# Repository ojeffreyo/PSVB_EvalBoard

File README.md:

# PSVB_EvalBoard
Hardware for SoC test designed by myself.

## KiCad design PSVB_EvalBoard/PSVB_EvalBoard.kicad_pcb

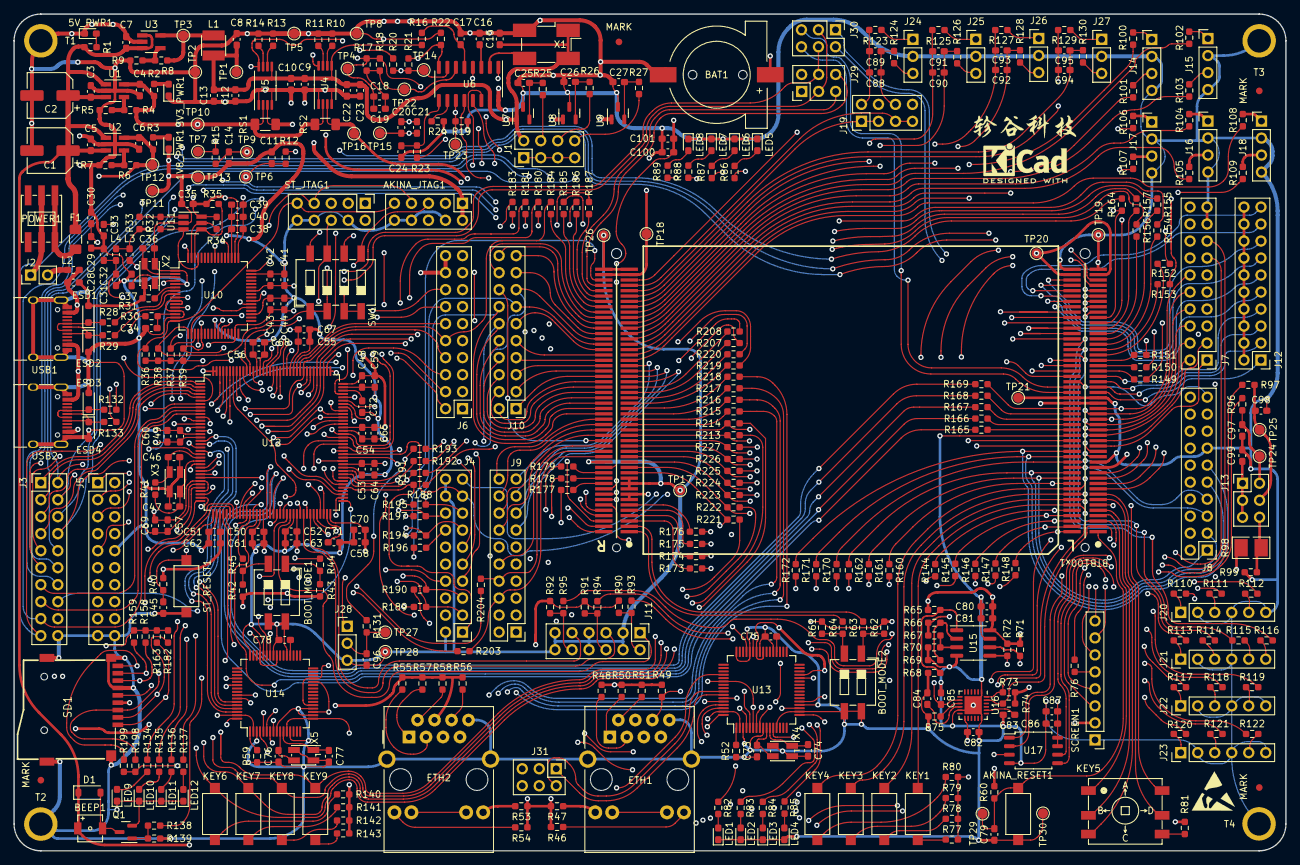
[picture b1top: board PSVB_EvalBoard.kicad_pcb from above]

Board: 4 copper layers, 190.0 x 125.0 mm, 463 parts (0 on the bottom side), 461 nets.

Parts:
1V8_PWR1: 0603 1V8_PWR; LED_0603_1608Metric_Pad1.05x0.95mm_HandSolder
3V3_PWR1: 0603 3V3_LED; LED_0603_1608Metric_Pad1.05x0.95mm_HandSolder
5V_PWR1: 0603 5V_LED; LED_0603_1608Metric_Pad1.05x0.95mm_HandSolder
AKINA_JTAG1: PinHeader_2x05_P2.54mm_Vertical
AKINA_RESET1: KEY; SW_SPST_CK_RS282G05A3
BAT1: CR1220-2; CR1220_Holder
BEEP1: BUZZER; BEEP_4317
BOOT_MODE1, BOOT_MODE2: SW_SMD_2P-2.54mm; SW_DIP_SPSTx02_Slide_6.7x6.64mm_W8.61mm_P2.54mm_LowProfile
BTB100x1: BTB100PINx2_IC_Adapter; BTB100PINx2_FemaleConnector
C1: 47uF; CP_Elec_6.3x7.7
C2: 22uF; CP_Elec_6.3x7.7
C3, C4, C5, C6, C7, C8: 0603 1uF/16V; C_0603_1608Metric_Pad1.08x0.95mm_HandSolder
C9: 0603 0.1uF/1%; C_0603_1608Metric_Pad1.08x0.95mm_HandSolder
C10, C17: 0603 4.7uF/1%; C_0603_1608Metric_Pad1.08x0.95mm_HandSolder
C11, C12, C14, C18, C19, C20, C21, C23, C29, C31, C34, C35, C45, C48, C71, C72, C75, C78, C79: 0603 0.1uF/16V; C_0603_1608Metric_Pad1.08x0.95mm_HandSolder
C13, C22, C24, C30, C32, C59: 0603 4.7uF/16V; C_0603_1608Metric_Pad1.08x0.95mm_HandSolder
C15: 0603 0.01uF/16V; C_0603_1608Metric_Pad1.08x0.95mm_HandSolder
C16: 0603 30P/16V; C_0603_1608Metric_Pad1.08x0.95mm_HandSolder
C25, C26, C27, C28: 0603 10uF/16V; C_0603_1608Metric_Pad1.08x0.95mm_HandSolder
C33: 0603 3.3uF/16V; C_0603_1608Metric_Pad1.08x0.95mm_HandSolder
C36, C37: 0603 27pF/16V; C_0603_1608Metric_Pad1.08x0.95mm_HandSolder
C38, C39, C40, C41, C42, C43, C44, C49, C50, C51, C52, C53, C54, C55, C56, C57, C58, C80, C81, C84, C85, C86, C87, C88, C89, C90, C91, C92, C93, C94, C95, C96, C97, C98, C99, C100: 0.1uF; C_0603_1608Metric_Pad1.08x0.95mm_HandSolder
C46, C47: 0603 10pF/16V; C_0603_1608Metric_Pad1.08x0.95mm_HandSolder
C60, C61, C62, C63, C64, C65, C67, C68, C69, C70: 4.7uF; C_0603_1608Metric_Pad1.08x0.95mm_HandSolder
C73, C74, C76, C77: 0603 20PF/16V; C_0603_1608Metric_Pad1.08x0.95mm_HandSolder
C82: 0.01uF; C_0603_1608Metric_Pad1.08x0.95mm_HandSolder
C83: 2.2nF; C_0603_1608Metric_Pad1.08x0.95mm_HandSolder
C101: 10uF; C_0603_1608Metric_Pad1.08x0.95mm_HandSolder
D1: 1N4148; D_SOD-123
ESD1, ESD2, ESD3, ESD4: SD24C-TP; D_SOD-323_HandSoldering
ETH1, ETH2: HR911105A; RJ45_HanRun_HR911105A
F1: 1206 10V/2A; Fuse_1206_3216Metric_Pad1.42x1.75mm_HandSolder
J1, J19: PinHeader_2x04_P2.54mm_Vertical
J2: PIN2; PinHeader_1x02_P2.54mm_Vertical
J3, J4, J5, J6, J7, J8, J9, J10, J12: PIN20; PinHeader_2x10_P2.54mm_Vertical
J11: PIN12_2x6; PinHeader_2x06_P2.54mm_Vertical
J13, J29, J30, J31: PIN6_2x3; PinHeader_2x03_P2.54mm_Vertical
J14, J15, J16, J17, J18: PinHeader_1x04_P2.54mm_Vertical
J20, J21, J22, J23: PinHeader_1x06_P2.54mm_Vertical
J24, J25, J26, J27, J28: PinHeader_1x03_P2.54mm_Vertical
KEY1, KEY2, KEY3, KEY4, KEY6, KEY7, KEY8, KEY9: SW_Push; SW_SPST_CK_RS282G05A3
KEY5: 5Axises_KEY; 5Axises_Key
L1: 2.2uH/1A; SWPA3010
L2, L3, L4: 6.8nH/500mA; L_0603_1608Metric_Pad1.05x0.95mm_HandSolder
LED1, LED2: YELLOW; LED_0603_1608Metric_Pad1.05x0.95mm_HandSolder
LED3, LED4, LED5, LED6, LED7, LED8, LED9, LED10, LED11, LED12: LD271; LED_0603_1608Metric_Pad1.05x0.95mm_HandSolder
MARK: Fiducial_1mm_Mask2mm
MARK#2, MARK#3, MARK#4: Fiducial_1mm_Mask2mm
POWER1: SW_SELF_LOCK_5.8mm-5.8mm-10mm; SelfLock_Switch
Q1: S9013; SOT-23
R1: 0603 5K/1%; R_0603_1608Metric_Pad0.98x0.95mm_HandSolder
R2, R3, R134, R135, R136, R137, R138: 0603 1K/1%; R_0603_1608Metric_Pad0.98x0.95mm_HandSolder
R4, R8: 0603 500K/1%; R_0603_1608Metric_Pad0.98x0.95mm_HandSolder
R5, R7: 0603 160K/1%; R_0603_1608Metric_Pad0.98x0.95mm_HandSolder
R6: 0603 200K/1%; R_0603_1608Metric_Pad0.98x0.95mm_HandSolder
R9: 0603 160K/16V; R_0603_1608Metric_Pad0.98x0.95mm_HandSolder
R10, R11, R12, R13, R14, R15, R17, R18, R19, R20, R21, R22, R23, R24, R25, R26, R27, R28, R29: 0603 0R/1%; R_0603_1608Metric_Pad0.98x0.95mm_HandSolder
R16, R30, R33, R34, R35, R36, R37, R38, R39, R40, R42, R43, R44, R45, R60, R61, R62, R63, R64, R76, R139, R140, R141, R142, R143, R144, R145, R146, R147, R148, R149, R150, R151, R152, R153, R154, R155, R156, R157, R160, R161, R162, R164, R165, R166, R167, R168, R169, R170, R171, R172, R173, R174, R175, R176, R177, R178, R179, R180, R181, R183, R184, R185, R186, R187, R188, R189, R190, R191, R192, R193, R194, R195, R196, R197, R203, R204, R207, R208, R213, R214, R215, R216, R217, R218, R219, R220, R221, R222, R223, R224, R225, R226, R227: 0603 10K/1%; R_0603_1608Metric_Pad0.98x0.95mm_HandSolder
R31: 0603 12K/1%; R_0603_1608Metric_Pad0.98x0.95mm_HandSolder
R32: 0603 2K/1%; R_0603_1608Metric_Pad0.98x0.95mm_HandSolder
R41: 0603 1M/1%; R_0603_1608Metric_Pad0.98x0.95mm_HandSolder
R46, R47, R53, R54: 510R/1%; R_0603_1608Metric_Pad0.98x0.95mm_HandSolder
R48, R49, R50, R51, R55, R56, R57, R58: 49R9/1%; R_0603_1608Metric_Pad0.98x0.95mm_HandSolder
R52, R59: 18K/1%; R_0603_1608Metric_Pad0.98x0.95mm_HandSolder
R65, R66, R67, R68, R69, R70, R71, R72, R73, R74, R77, R78, R79, R80, R81, R90, R91, R92, R96, R97, R99, R123, R124, R125, R126, R127, R128, R129, R130: 10K/1%; R_0603_1608Metric_Pad0.98x0.95mm_HandSolder
R75: 4.7K/1%; R_0603_1608Metric_Pad0.98x0.95mm_HandSolder
R82, R83, R84, R85, R86, R87, R88, R89: 1K/1%; R_0603_1608Metric_Pad0.98x0.95mm_HandSolder
R93, R94, R95, R100, R101, R102, R103, R104, R105, R106, R107, R108, R109, R110, R111, R112, R113, R114, R115, R116, R117, R118, R119, R120, R121, R122, R132, R133: 0R/1%; R_0603_1608Metric_Pad0.98x0.95mm_HandSolder
R98: A1050; GT36516
R131: 0603 100R/1%; R_0603_1608Metric_Pad0.98x0.95mm_HandSolder
R158, R159, R163, R182, R198, R199: 0603 47K/1%; R_0603_1608Metric_Pad0.98x0.95mm_HandSolder
RS1, RS2: 0603 10mR/1%; R_1206_3216Metric_Pad1.30x1.75mm_HandSolder
SCREEN1: 2.4In_TFT_Screen; PinHeader_1x08_P2.54mm_Vertical
SD1: TF-SMD_TF-02
ST_JTAG1: PinHeader_2x05_P2.54mm_Vertical
ST_RESET1: KEY; SW_SPST_CK_RS282G05A3
SW1: SW_DIP_SPSTx04_Slide_6.7x11.72mm_W8.61mm_P2.54mm_LowProfile
T1, T2, T3, T4: M3_Whole
TP1, TP2, TP3, TP4, TP5, TP6, TP7, TP8, TP9, TP10, TP11, TP12, TP13, TP14, TP15, TP16, TP17, TP18, TP19, TP20, TP21, TP22, TP23, TP24, TP25, TP26, TP27, TP28, TP29, TP30: TestPoint_1.5mm; TestPoint_Pad_D1.5mm
U1, U2, U3: SGM2036-ADJ; SOT-23-5_HandSoldering
U4, U5: INA240A1PWR; TSSOP-8_4.4x3mm_P0.65mm
U6: TM7707; SOIC-16_3.9x9.9mm_P1.27mm
U7: REF3030; SOT-23
U8: REF3025; SOT-23
U9: REF3012; SOT-23
U10: LQFP-64_10x10mm_P0.5mm
U11: 93LC56BT-IOT; SOT-23-6_Handsoldering
U12: STM32F429ZETx; LQFP-144_20x20mm_P0.5mm
U13, U14: CH395Q; LQFP-64_10x10mm_P0.5mm
U15: 24LC64ISN; SOIC-8_3.9x4.9mm_P1.27mm
U16: MPU6050; QFN-24-1EP_4x4mm_P0.5mm_EP2.7x2.6mm
U17: W25Q128JVSIQ; SOIC-8_5.275x5.275mm_P1.27mm
USB1, USB2: USB_C_16PIN-Connector; USB_C_PIN16
X1: 2.4576Mhz; Oscillator_SMD_EuroQuartz_XO91-4Pin_7.0x5.0mm_HandSoldering
X2: 12Mhz_Passive_3225; Oscillator_SMD_EuroQuartz_XO32-4Pin_3.2x2.5mm_HandSoldering
X3: 16Mhz_Passive_3225; Oscillator_SMD_EuroQuartz_XO32-4Pin_3.2x2.5mm_HandSoldering
X4, X5: 30Mhz_3225; Oscillator_SMD_EuroQuartz_XO32-4Pin_3.2x2.5mm_HandSoldering

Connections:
+1V8: C6.1, R3.2, R6.2, R46.2, R47.2, R53.2, R54.2, TP12.1, U2.5 (VOUT), U13.6 (VCC18), U13.19 (VCC18), U13.28 (VCC18), U13.43 (VCC18), U13.54 (VCC18), U13.64 (VCC18), U14.6 (VCC18), U14.19 (VCC18), U14.28 (VCC18), U14.43 (VCC18), U14.54 (VCC18), U14.64 (VCC18)
+3.3VA: C8.1, C9.2, C10.2, C12.2, C13.2, C15.1, C22.1, C23.1, J1.2, L1.2, R16.2, TP1.1, U4.5 (VCC), U5.5 (VCC), U6.15 (VDD), U7.1 (IN), U8.1 (IN), U9.1 (IN), X1.1 (OE), X1.4 (VDD)
+3V3: AKINA_JTAG1.1, AKINA_JTAG1.2, C4.1, C35.1, C41.2, C42.2, C43.2, C44.2, C48.1, C49.1, C50.1, C51.1, C52.1, C53.1, C54.1, C55.1, C56.1, C57.1, C58.1, C59.1, C60.1, C61.1, C62.1, C63.1, C64.1, C65.1, C67.1, C68.1, C69.1, C70.1, C80.1, C81.1, C82.1, C85.1, C86.1, C87.1, ETH1.4 (P4/CT), ETH1.5 (P5/CT), ETH2.4 (P4/CT), ETH2.5 (P5/CT), J5.2, J5.4, J6.18, J6.20, L3.2, L4.2, R2.2, R4.2, R30.1, R33.1, R34.2, R35.2, R36.1, R37.1, R38.1, R39.1, R40.1, R42.2, R43.2, R48.1, R49.1, R50.1, R51.1, R55.1, R56.1, R57.1, R58.1, R61.2, R62.2, R65.1, R66.1, R67.1, R71.1, R72.1, R73.1, R74.1, R77.2, R78.2, R79.2, R80.2, R81.2, R90.2, R91.2, R92.2, R98.1, R140.2, R141.2, R142.2, R143.2, R158.2, R159.2, R163.2, R182.2, R198.2, R199.2, RS1.1, RS2.1, SCREEN1.2 (VCC), SD1.4 (VDD), ST_JTAG1.1, ST_JTAG1.2, TP10.1, U1.5 (VOUT), U4.2 (IN+), U5.2 (IN+), U10.20 (VCCIO), U10.31 (VCCIO), U10.42 (VCCIO), U10.50 (VREGIN), U10.56 (VCCIO), U11.6 (VCC), U12.17 (VDD), U12.30 (VDD), U12.33 (VDDA), U12.39 (VDD), U12.52 (VDD), U12.62 (VDD), U12.72 (VDD), U12.84 (VDD), U12.95 (VDD), U12.108 (VDD), U12.121 (VDD), U12.131 (VDD), U12.143 (PDR_ON), U12.144 (VDD), U13.2 (VCC33), U13.12 (VCC33), U13.17 (VCC33), U13.21 (VCC33), U13.29 (VCC33), U13.40 (VCC33), U13.42 (VCC33), U13.45 (VCC33), U13.63 (VCC33), U14.2 (VCC33), U14.12 (VCC33), U14.17 (VCC33), U14.21 (VCC33), U14.29 (VCC33), U14.40 (VCC33), U14.42 (VCC33), U14.45 (VCC33), U14.63 (VCC33), U15.8 (VCC), U16.8 (VLOGIC), U16.13 (VDD), U17.3 (~WP(IO2)), U17.7 (~HOLD/RESET(IO3)), U17.8 (VCC)
+5V: BEEP1.1 (+), BTB100x1.107, BTB100x1.108, C1.1, C2.1, C3.1, C5.1, C7.1, D1.1 (K), F1.1, R1.1, U1.1 (VIN), U1.3 (EN), U2.1 (VIN), U2.3 (EN), U3.1 (VIN), U3.3 (EN)
/AD0: AKINA_JTAG1.9, BTB100x1.154, R36.2, ST_JTAG1.9, U10.16 (ADBUS0), U12.109 (PA14)
/AD1: AKINA_JTAG1.5, BTB100x1.152, R38.2, SW1.1, SW1.2, SW1.5, U10.17 (ADBUS1)
/AD2: SW1.3, SW1.4, U10.18 (ADBUS2)
/AD3: AKINA_JTAG1.7, BTB100x1.153, R37.2, ST_JTAG1.7, U10.19 (ADBUS3), U12.105 (PA13)
/AD4: AKINA_JTAG1.3, BTB100x1.155, R39.2, ST_JTAG1.3, U10.21 (ADBUS4), U12.134 (PB4)
/ADC12_IN14: C14.1, R15.2, TP9.1, U12.44 (PC4)
/ADC12_IN15: C11.2, R12.2, TP6.1, U12.45 (PC5)
/ADC123_IN13: J28.1, U12.29 (PC3)
/AIN1+: C20.1, C21.1, R20.2, R21.2, TP14.1, U6.7 (AIN1(+))
/AIN1-: C20.2, C21.2, R21.1, R22.2, TP15.1, U6.8 (AIN1(-))
/AIN2+: C18.1, C19.1, R17.2, R18.2, TP22.1, U6.6 (AIN2(+))
/AIN2-: C18.2, C19.2, R12.1, R17.1, R18.1, R19.2, TP4.1, TP23.1, U4.8 (OUT), U6.11 (AIN2(-))
/AKINA_ADC_IN4: BTB100x1.27, J12.1
/AKINA_ADC_IN5: BTB100x1.28, J12.3
/AKINA_ADC_IN6: BTB100x1.29, J12.5
/AKINA_ADC_IN7: BTB100x1.30, J12.7
/AKINA_ADC_IN8: BTB100x1.93, J12.9
/AKINA_ADC_IN9: BTB100x1.94, J12.11
/AKINA_ADC_IN10: BTB100x1.97, J12.13
/AKINA_ADC_IN11: BTB100x1.98, J12.15
/AKINA_ADC_IN12: BTB100x1.96, J12.17
/AKINA_ADC_IN13: BTB100x1.95, J12.19
/AKINA_BLK: BTB100x1.21, J7.6, SCREEN1.8 (BLK)
/AKINA_BOOT0: BTB100x1.101, R64.2
/AKINA_BOOT1: BTB100x1.102, R63.2
/AKINA_CMP1_IN: BTB100x1.86, R116.1
/AKINA_CMP1_IP1: BTB100x1.80, R110.1
/AKINA_CMP1_IP2: BTB100x1.81, R111.1
/AKINA_CMP1_IP3: BTB100x1.82, R112.1
/AKINA_CMP1_IP4: BTB100x1.84, R114.1
/AKINA_CMP1_IP5: BTB100x1.85, R115.1
/AKINA_CMP1/2_REF: BTB100x1.83, R113.1
/AKINA_CMP2_IN: BTB100x1.92, R122.1
/AKINA_CMP2_IP1: BTB100x1.87, R117.1
/AKINA_CMP2_IP2: BTB100x1.88, R118.1
/AKINA_CMP2_IP3: BTB100x1.89, R119.1
/AKINA_CMP2_IP4: BTB100x1.90, R120.1
/AKINA_CMP2_IP5: BTB100x1.91, R121.1
/AKINA_D_C: BTB100x1.20, J7.4, SCREEN1.6 (D/C)
/AKINA_ETH_ELINK: ETH1.10, ETH1.11, U13.52 (ELINK#)
/AKINA_ETH_SCK: BTB100x1.170, J9.16, U13.60 (SCK)
/AKINA_ETH_SCS: BTB100x1.169, J9.14, U13.59 (SCS)
/AKINA_ETH_SDI: BTB100x1.171, J9.18, U13.61 (SDI)
/AKINA_ETH_SDO: BTB100x1.172, J9.20, U13.62 (SDO)
/AKINA_HALL_CH1: BTB100x1.46, R93.2
/AKINA_HALL_CH2: BTB100x1.47, R94.2
/AKINA_HALL_CH3: BTB100x1.48, R95.2
/AKINA_I2C1_SCL: BTB100x1.17, J7.1, R71.2, U15.6 (SCL)
/AKINA_I2C1_SDA: BTB100x1.18, J7.3, R72.2, U15.5 (SDA)
/AKINA_I2C2_SCL: BTB100x1.2, J7.13, R74.2, U16.23 (SCL)
/AKINA_I2C2_SDA: BTB100x1.3, J7.15, R73.2, U16.24 (SDA)
/AKINA_JTDO: AKINA_JTAG1.6, BTB100x1.151, SW1.6
/AKINA_KEY1: BTB100x1.56, J8.12, KEY1.1
/AKINA_KEY2: BTB100x1.57, J8.14, KEY2.1
/AKINA_KEY3: BTB100x1.58, J8.16, KEY3.1
/AKINA_KEY4: BTB100x1.59, J8.18, KEY4.1
/AKINA_KEY_A: BTB100x1.4, KEY5.1 (A)
/AKINA_KEY_B: BTB100x1.5, KEY5.2 (B)
/AKINA_KEY_C: BTB100x1.7, KEY5.3 (C)
/AKINA_KEY_CENTER: BTB100x1.6, KEY5.6 (CENTER)
/AKINA_KEY_D: BTB100x1.8, KEY5.5 (D)
/AKINA_LED0: BTB100x1.42, J7.14, R89.1
/AKINA_LED1: BTB100x1.43, J7.16, R88.1
/AKINA_LED2: BTB100x1.44, J7.18, R87.1
/AKINA_LED3: BTB100x1.45, J7.20, R86.1
/AKINA_LED4: BTB100x1.156, R85.1
/AKINA_LED5: BTB100x1.157, R84.1
/AKINA_LED6: BTB100x1.158, R83.1
/AKINA_LED7: BTB100x1.159, R82.1
/AKINA_OPAMP1_IN: C88.1, C89.1, J19.6, R124.1
/AKINA_OPAMP1_IP: C88.2, C89.2, J19.2, R123.1
/AKINA_OPAMP2_IN: BTB100x1.142, C90.1, C91.1, R126.1
/AKINA_OPAMP2_IP: BTB100x1.143, C90.2, C91.2, R125.1
/AKINA_OPAMP3_IN: BTB100x1.140, C92.1, C93.1, R128.1
/AKINA_OPAMP3_IP: BTB100x1.141, C92.2, C93.2, R127.1
/AKINA_OPAMP4_IN: BTB100x1.145, C94.1, C95.1, R130.1
/AKINA_OPAMP4_IP: BTB100x1.144, C94.2, C95.2, R129.1
/AKINA_OPA_OUT: BTB100x1.198, R131.2
/AKINA_PA9: BTB100x1.147, J19.5, J19.7
/AKINA_PA10: BTB100x1.146, J19.1, J19.3
/AKINA_RESET: AKINA_RESET1.2, BTB100x1.1, C79.1, R60.1, TP29.1
/AKINA_SCREEN_RST: BTB100x1.19, J7.2, R76.2
/AKINA_SPI1_MISO: BTB100x1.10, J7.7, U17.2 (DO(IO1))
/AKINA_SPI1_MOSI: BTB100x1.11, J7.9, U17.5 (DI(IO0))
/AKINA_SPI1_NSS: BTB100x1.12, J7.11, U17.1 (~CS)
/AKINA_SPI1_SCK: BTB100x1.9, J7.5, U17.6 (CLK)
/AKINA_SPI2_MOSI: BTB100x1.23, J7.10, SCREEN1.4 (SDA)
/AKINA_SPI2_NSS: BTB100x1.24, J7.12, SCREEN1.7 (CS)
/AKINA_SPI2_SCK: BTB100x1.22, J7.8, SCREEN1.3 (SCL)
/AKINA_USART1_RX: BTB100x1.16, J29.2
/AKINA_USART1_TX: BTB100x1.15, J29.1
/AKINA_USART2_RX: BTB100x1.197, J29.6
/AKINA_USART2_TX: BTB100x1.196, J29.5
/AKINA_USART3_RX: BTB100x1.68, J30.2
/AKINA_USART3_TX: BTB100x1.67, J30.1
/AKINA_USART4_RX: BTB100x1.78, J30.6
/AKINA_USART4_TX: BTB100x1.77, J30.5
/BTB_PA0: BTB100x1.103, R173.1
/BTB_PA1: BTB100x1.104, R174.1
/BTB_PA2: BTB100x1.105, R175.1
/BTB_PA3: BTB100x1.106, R176.1
/BTB_PB0: BTB100x1.165, J9.6, R203.1
/BTB_PB1: BTB100x1.166, J9.8, R204.1
/BTB_PB2: BTB100x1.167, J9.10
/BTB_PB5: BTB100x1.128, R208.1
/BTB_PC0: BTB100x1.60, J8.20, R160.1
/BTB_PC1: BTB100x1.61, J8.1, R161.1
/BTB_PC2: BTB100x1.62, J8.3, R162.1
/BTB_PC6: BTB100x1.173, J10.14, R196.1
/BTB_PC7: BTB100x1.174, J10.12, R197.1
/BTB_PC13: BTB100x1.64, J8.7, R170.2
/BTB_PC14: BTB100x1.65, J8.9, R171.2
/BTB_PC15: BTB100x1.66, J8.11, R172.2
/BTB_PD0: BTB100x1.188, J10.17, R180.1
/BTB_PD1: BTB100x1.189, J10.19, R181.1
/BTB_PD3: BTB100x1.190, J10.20, R183.1
/BTB_PD4: BTB100x1.192, R184.1
/BTB_PD5: BTB100x1.193, R185.1
/BTB_PD6: BTB100x1.194, R186.1
/BTB_PD7: BTB100x1.195, R187.1
/BTB_PD8: BTB100x1.180, J10.1, R188.1
/BTB_PD9: BTB100x1.181, J10.3, R189.1
/BTB_PD10: BTB100x1.182, J10.5, R190.1
/BTB_PD11: BTB100x1.183, J10.7, R191.1
/BTB_PD12: BTB100x1.184, J10.9, R192.1
/BTB_PD13: BTB100x1.185, J10.11, R193.1
/BTB_PD14: BTB100x1.186, J10.13, R194.1
/BTB_PD15: BTB100x1.187, J10.15, R195.1
/BTB_PE0: BTB100x1.125, R219.1
/BTB_PE1: BTB100x1.126, R220.1
/BTB_PE2: BTB100x1.51, J8.2, R148.2
/BTB_PE3: BTB100x1.52, J8.4, R147.2
/BTB_PE4: BTB100x1.53, J8.6, R146.2
/BTB_PE5: BTB100x1.54, J8.8, R145.2
/BTB_PE6: BTB100x1.55, J8.10, R144.2
/BTB_PE7: BTB100x1.119, J9.9, R213.1
/BTB_PE8: BTB100x1.120, J9.11, R214.1
/BTB_PE10: BTB100x1.121, R215.1
/BTB_PE12: BTB100x1.122, R216.1
/BTB_PE14: BTB100x1.123, R217.1
/BTB_PE15: BTB100x1.124, R218.1
/BTB_PF0: BTB100x1.31, R149.2
/BTB_PF1: BTB100x1.32, R150.2
/BTB_PF2: BTB100x1.33, R151.2
/BTB_PF3: BTB100x1.34, R152.2
/BTB_PF4: BTB100x1.35, R153.2
/BTB_PF5: BTB100x1.36, R154.2
/BTB_PF6: BTB100x1.37, R155.2
/BTB_PF7: BTB100x1.38, R156.2
/BTB_PF8: BTB100x1.39, R157.2
/BTB_PF9: BTB100x1.40, J8.15
/BTB_PF10: BTB100x1.41, J8.17, R164.1
/BTB_PF11: BTB100x1.70, R165.1
/BTB_PF12: BTB100x1.71, R166.1
/BTB_PF13: BTB100x1.72, R167.1
/BTB_PF14: BTB100x1.73, R168.1
/BTB_PF15: BTB100x1.74, R169.1
/BTB_PG0: BTB100x1.112, J9.1, R221.1
/BTB_PG1: BTB100x1.113, J9.2, R222.1
/BTB_PG2: BTB100x1.114, J9.4, R223.1
/BTB_PG3: BTB100x1.115, J9.3, R224.1
/BTB_PG4: BTB100x1.116, J9.5, R225.1
/BTB_PG5: BTB100x1.117, J9.7, R226.1
/BTB_PG6: BTB100x1.118, J9.12, R227.1
/BTB_PG9: BTB100x1.160, R177.1
/BTB_PG10: BTB100x1.161, R178.1
/BTB_PG11: BTB100x1.162, R179.1
/BTB_PG15: BTB100x1.127, R207.1
/CMP1_IN: J21.5, R115.2
/CMP1_IP1: J20.1, R110.2
/CMP1_IP2: J20.3, R111.2
/CMP1_IP3: J20.5, R112.2
/CMP1_IP4: J21.1, R113.2
/CMP1_IP5: J21.3, R114.2
/CMP2_IN: J23.5, R122.2
/CMP2_IP1: J22.1, R117.2
/CMP2_IP2: J22.3, R118.2
/CMP2_IP3: J22.5, R119.2
/CMP2_IP4: J23.1, R120.2
/CMP2_IP5: J23.3, R121.2
/DUT_+3.3V_1: BTB100x1.25, BTB100x1.49, BTB100x1.75, BTB100x1.99, BTB100x1.149, BTB100x1.199, R60.2, RS1.2, TP18.1, TP20.1, U5.3 (IN-)
/DUT_VBAT: BAT1.1 (+), BTB100x1.163, C100.1, C101.1, U12.6 (VBAT)
/DUT_VDDA_3.3V_1: BTB100x1.13, RS2.2, TP16.1, U4.3 (IN-)
/ETH1_RXD: J31.2, U13.57 (RXD)
/ETH1_RXN: ETH1.6 (P6/RD-), R49.2, U13.5 (RXN)
/ETH1_RXP: ETH1.3 (P3/RD+), R48.2, U13.4 (RXP)
/ETH1_TXD: J31.1, U13.58 (TXD)
/ETH1_TXN: ETH1.2 (P2/TD-), R51.2, U13.8 (TXN)
/ETH1_TXP: ETH1.1 (P1/TD+), R50.2, U13.7 (TXP)
/ETH2_RXD: J31.6, U14.57 (RXD)
/ETH2_RXN: ETH2.6 (P6/RD-), R56.2, U14.5 (RXN)
/ETH2_RXP: ETH2.3 (P3/RD+), R55.2, U14.4 (RXP)
/ETH2_TXD: J31.5, U14.58 (TXD)
/ETH2_TXN: ETH2.2 (P2/TD-), R58.2, U14.8 (TXN)
/ETH2_TXP: ETH2.1 (P1/TD+), R57.2, U14.7 (TXP)
/EXP_PIN1: BTB100x1.63, J8.5
/EXP_PIN2: BTB100x1.79, J8.19
/EXP_PIN3: BTB100x1.129, J9.13
/EXP_PIN4: BTB100x1.130, J9.15
/EXP_PIN5: BTB100x1.131, J9.17
/EXP_PIN6: BTB100x1.132, J9.19
/EXP_PIN7: BTB100x1.168, J10.16
/EXP_PIN8: BTB100x1.175, J10.10
/EXP_PIN9: BTB100x1.176, J10.8
/EXP_PIN10: BTB100x1.177, J10.6
/EXP_PIN11: BTB100x1.178, J10.4
/EXP_PIN12: BTB100x1.179, J10.2
/EXP_PIN13: BTB100x1.191, J10.18
/FT_USART2_RX: J29.3, J30.3, U10.27 (BDBUS1)
/FT_USART2_TX: J29.4, J30.4, U10.26 (BDBUS0)
/FT_USART3_RX: U10.39 (CDBUS1), U12.69 (PB10)
/FT_USART3_TX: U10.38 (CDBUS0), U12.70 (PB11)
/FT_USART4_RX: J31.3, U10.52 (DDBUS1)
/FT_USART4_TX: J31.4, U10.48 (DDBUS0)
/INA240_Output1: R15.1, R20.1, TP7.1, U5.8 (OUT)
/MCPWM_CH1: BTB100x1.134, R100.1
/MCPWM_CH1N: BTB100x1.135, R101.1
/MCPWM_CH2: BTB100x1.139, R102.1
/MCPWM_CH2N: BTB100x1.138, R103.1
/MCPWM_CH3: BTB100x1.137, R104.1
/MCPWM_CH3N: BTB100x1.136, R105.1
/MCPWM_CH4: J19.4, R106.1
/MCPWM_CH4N: J19.8, R107.1
/MC_BKIN_0: BTB100x1.133, R108.1
/MC_BKIN_1: BTB100x1.148, R109.1
/OPAMP1_IN: J24.3, R124.2
/OPAMP1_IP: J24.1, R123.2
/OPAMP2_IN: J25.3, R126.2
/OPAMP2_IP: J25.1, R125.2
/OPAMP3_IN: J26.3, R128.2
/OPAMP3_IP: J26.1, R127.2
/OPAMP4_IN: J27.3, R130.2
/OPAMP4_IP: J27.1, R129.2
/PA0: J5.7, KEY6.1, R173.2, U12.34 (PA0)
/PA1: J5.9, KEY7.1, R174.2, U12.35 (PA1)
/PA2: J5.11, KEY8.1, R175.2, U12.36 (PA2)
/PA3: J5.13, KEY9.1, R176.2, U12.37 (PA3)
/PA6: J5.15, U12.42 (PA6)
/PA7: J5.17, U12.43 (PA7)
/PA8: J6.5, U12.100 (PA8)
/PA9: J6.7, U12.101 (PA9)
/PA10: J6.9, U12.102 (PA10)
/PA11: J6.11, U12.103 (PA11)
/PA12: J6.13, U12.104 (PA12)
/PB0: J5.6, R203.2, U12.46 (PB0)
/PB1: J5.8, R204.2, U12.47 (PB1)
/PB5: R208.2, U12.135 (PB5)
/PB6: R137.1, U12.136 (PB6)
/PB7: R136.1, U12.137 (PB7)
/PB8: R135.1, U12.139 (PB8)
/PB9: R134.1, U12.140 (PB9)
/PC0: J5.1, R160.2, U12.26 (PC0)
/PC1: J5.3, R161.2, U12.27 (PC1)
/PC2: J5.5, R162.2, U12.28 (PC2)
/PC6: J4.14, R196.2, U12.96 (PC6)
/PC7: J4.16, R197.2, U12.97 (PC7)
/PC8: J6.1, R158.1, SD1.7 (DAT0(D0)), U12.98 (PC8)
/PC9: J6.3, R159.1, SD1.8 (DAT1(RSV)), U12.99 (PC9)
/PC10: J6.15, R163.1, SD1.1 (DAT2(RSV)), U12.111 (PC10)
/PC11: J6.17, R182.1, SD1.2 (CDAT3/CS), U12.112 (PC11)
/PC12: J6.19, SD1.5 (CLK), U12.113 (PC12)
/PC13: J3.11, R170.1, U12.7 (PC13)
/PC14: J3.13, R171.1, U12.8 (PC14)
/PC15: J3.15, R172.1, U12.9 (PC15)
/PD0: J6.2, R180.2, U12.114 (PD0)
/PD1: J6.4, R181.2, U12.115 (PD1)
/PD2: J6.6, R198.1, SD1.3 (CMD), U12.116 (PD2)
/PD3: J6.8, R183.2, R199.1, SD1.9 (CD), U12.117 (PD3)
/PD4: J6.10, R184.2, U12.118 (PD4)
/PD5: J6.12, R185.2, U12.119 (PD5)
/PD6: J6.14, R186.2, U12.122 (PD6)
/PD7: J6.16, R187.2, U12.123 (PD7)
/PD8: J4.1, R188.2, U12.77 (PD8)
/PD9: J4.3, R189.2, U12.78 (PD9)
/PD10: J4.5, R190.2, U12.79 (PD10)
/PD11: J4.7, R191.2, U12.80 (PD11)
/PD12: J4.9, R192.2, U12.81 (PD12)
/PD13: J4.11, R193.2, U12.82 (PD13)
/PD14: J4.13, R194.2, U12.85 (PD14)
/PD15: J4.15, R195.2, U12.86 (PD15)
/PE0: R219.2, U12.141 (PE0)
/PE1: R220.2, U12.142 (PE1)
/PE2: J3.1, R148.1, U12.1 (PE2)
/PE3: J3.3, R147.1, U12.2 (PE3)
/PE4: J3.5, R146.1, U12.3 (PE4)
/PE5: J3.7, R145.1, U12.4 (PE5)
/PE6: J3.9, R144.1, U12.5 (PE6)
/PE7: J5.16, R213.2, U12.58 (PE7)
/PE8: J5.18, R214.2, U12.59 (PE8)
/PE10: R215.2, U12.63 (PE10)
/PE12: R216.2, U12.65 (PE12)
/PE14: R217.2, U12.67 (PE14)
/PE15: R218.2, U12.68 (PE15)
/PF0: J3.17, R149.1, U12.10 (PF0)
/PF1: J3.19, R150.1, U12.11 (PF1)
/PF2: J3.2, R151.1, U12.12 (PF2)
/PF3: J3.4, R152.1, U12.13 (PF3)
/PF4: J3.6, R153.1, U12.14 (PF4)
/PF5: J3.8, R154.1, U12.15 (PF5)
/PF6: J3.10, R155.1
/PF7: J3.12, R156.1
/PF8: J3.14, R157.1
/PF10: J3.18, R164.2, U12.22 (PF10)
/PF11: R165.2, U12.49 (PF11)
/PF12: R166.2, U12.50 (PF12)
/PF13: R167.2, U12.53 (PF13)
/PF14: R168.2, U12.54 (PF14)
/PF15: R169.2, U12.55 (PF15)
/PG0: J5.12, R221.2, U12.56 (PG0)
/PG1: J5.14, R222.2, U12.57 (PG1)
/PG2: J4.17, R223.2, U12.87 (PG2)
/PG3: J4.19, R224.2, U12.88 (PG3)
/PG4: J4.4, R225.2, U12.89 (PG4)
/PG5: J4.6, R226.2, U12.90 (PG5)
/PG6: J4.8, R227.2, U12.91 (PG6)
/PG7: J4.10, U6.12 (~DRDY), U12.92 (PG7)
/PG9: R177.2, U12.124 (PG9)
/PG10: R178.2, U12.125 (PG10)
/PG11: R179.2, U12.126 (PG11)
/PG15: R207.2, U12.132 (PG15)
/REF_1.25V: J1.8, R27.1
/REF_2.5V: J1.6, R26.1
/REF_3V: J1.4, R25.1
/STM32_BEEP: R138.1, U12.74 (PB13)
/STM32_BOOT0: R44.2, U12.138 (BOOT0)
/STM32_BOOT1: R45.2, U12.48 (PB2)
/STM32_DAC_OUT1: R96.1, U12.40 (PA4)
/STM32_DAC_OUT2: R97.1, U12.41 (PA5)
/STM32_ETH_ELINK: ETH2.10, ETH2.11, U14.52 (ELINK#)
/STM32_ETH_SCK: U12.19 (PF7), U14.60 (SCK)
/STM32_ETH_SCS: U12.18 (PF6), U14.59 (SCS)
/STM32_ETH_SDI: U12.20 (PF8), U14.61 (SDI)
/STM32_ETH_SDO: U12.21 (PF9), U14.62 (SDO)
/STM32_SPI6_MISO: U6.13 (DOUT), U12.127 (PG12)
/STM32_SPI6_MOSI: U6.14 (DIN), U12.129 (PG14)
/STM32_SPI6_NSS: J4.12, U6.4 (~CS), U12.93 (PG8)
/STM32_SPI6_SCK: U6.1 (SCLK), U12.128 (PG13)
/STM32_USB_DM: R132.2, U12.75 (PB14)
/STM32_USB_DP: R133.2, U12.76 (PB15)
/STM32_USB_ID: J3.16, U12.73 (PB12)
/ST_HALL_CH1: J11.1, U12.60 (PE9)
/ST_HALL_CH2: J11.5, U12.64 (PE11)
/ST_HALL_CH3: J11.9, U12.66 (PE13)
/ST_JTDI: ST_JTAG1.5, SW1.8, U12.110 (PA15)
/ST_JTDO: ST_JTAG1.6, SW1.7, U12.133 (PB3)
/TM7707_RST: C17.1, R16.1, U6.5 (~RESET)
/TP3: L1.1, R8.2, TP3.1, U3.5 (VOUT)
/TP24: C97.2, J13.2, R96.2, TP24.1
/TP25: C98.2, J13.4, R97.2, TP25.1
/TP27: C96.2, J28.2, R131.1, TP27.1
/USB_PWR_IN: C28.1, L2.1, USB1.2 (A4/B9), USB1.11 (A9/B4), USB2.2 (A4/B9), USB2.11 (A9/B4)
/VBUS: J2.1, POWER1.2, POWER1.5
/VCORE: C33.2, C38.2, C39.2, C40.2, U10.12 (VCORE), U10.37 (VCORE), U10.49 (VREGOUT), U10.64 (VCORE)
unnamed: 1V8_PWR1.2 (A), R3.1
unnamed: 3V3_PWR1.2 (A), R2.1
unnamed: 5V_PWR1.2 (A), R1.2
unnamed: BEEP1.2 (-), D1.2 (A), Q1.3 (C)
unnamed: BOOT_MODE1.1, R43.1, R44.1
unnamed: BOOT_MODE1.2, R42.1, R45.1
unnamed: BOOT_MODE2.1, R62.1, R63.1
unnamed: BOOT_MODE2.2, R61.1, R64.1
unnamed: C99.2, J12.2, J12.4, J12.6, J12.8, J12.10, J12.12, J12.14, J12.16, J12.18, J12.20, J13.1, J13.3, J13.5
unnamed: ESD1.1 (A1), R28.1, USB1.5 (B7), USB1.7 (A7)
unnamed: ESD2.1 (A1), R29.1, USB1.6 (A6), USB1.8 (B6)
unnamed: ESD3.1 (A1), R132.1, USB2.5 (B7), USB2.7 (A7)
unnamed: ESD4.1 (A1), R133.1, USB2.6 (A6), USB2.8 (B6)
unnamed: ETH1.9, R47.1
unnamed: ETH1.12, R46.1
unnamed: ETH2.9, R54.1
unnamed: ETH2.12, R53.1
unnamed: F1.2, POWER1.3, POWER1.6
unnamed: J1.1, J1.3, J1.5, J1.7, R23.2
unnamed: J2.2, L2.2
unnamed: J11.2, R90.1, R93.1
unnamed: J11.6, R91.1, R94.1
unnamed: J11.10, R92.1, R95.1
unnamed: J13.6, R98.2, R99.2
unnamed: J14.1, R100.2
unnamed: J14.3, R101.2
unnamed: J15.1, R102.2
unnamed: J15.3, R103.2
unnamed: J16.1, R104.2
unnamed: J16.3, R105.2
unnamed: J17.1, R106.2
unnamed: J17.3, R107.2
unnamed: J18.1, R108.2
unnamed: J18.3, R109.2
unnamed: J21.6, R116.2
unnamed: KEY1.2, R77.1
unnamed: KEY2.2, R78.1
unnamed: KEY3.2, R79.1
unnamed: KEY4.2, R80.1
unnamed: KEY5.4 (COMMON), R81.1
unnamed: KEY6.2, R140.1
unnamed: KEY7.2, R141.1
unnamed: KEY8.2, R142.1
unnamed: KEY9.2, R143.1
unnamed: LED1.2 (A), R82.2
unnamed: LED2.2 (A), R83.2
unnamed: LED3.2 (A), R84.2
unnamed: LED4.2 (A), R85.2
unnamed: LED5.2 (A), R86.2
unnamed: LED6.2 (A), R87.2
unnamed: LED7.2 (A), R88.2
unnamed: LED8.2 (A), R89.2
unnamed: LED9.2 (A), R134.2
unnamed: LED10.2 (A), R135.2
unnamed: LED11.2 (A), R136.2
unnamed: LED12.2 (A), R137.2
unnamed: Q1.1 (B), R138.2, R139.2
unnamed: R76.1, SCREEN1.5 (~RESET)
unnamed: R4.1, R5.2, U1.4 (BP/FB)
unnamed: R6.1, R7.2, U2.4 (BP/FB)
unnamed: R8.1, R9.2, U3.4 (BP/FB)
unnamed: R11.2, U4.7 (REF1)
unnamed: R10.2, U4.6 (REF2)
unnamed: R14.2, U5.7 (REF1)
unnamed: R13.2, U5.6 (REF2)
unnamed: U6.2 (MCLK_IN), X1.3 (OUT)
unnamed: C16.1, U6.3 (MCLK_OUT)
unnamed: C24.2, R23.1, U6.9 (REF_IN(+))
unnamed: R24.2, U6.10 (REF_IN(-))
unnamed: C25.2, R25.2, U7.2 (OUT)
unnamed: C26.2, R26.2, U8.2 (OUT)
unnamed: C27.2, R27.2, U9.2 (OUT)
unnamed: R28.2, U10.7 (DM)
unnamed: R29.2, U10.8 (DP)
unnamed: R35.1, U10.62 (EECLK), U11.4 (CLK)
unnamed: R34.1, U10.63 (EECS), U11.5 (CS)
unnamed: R32.2, U10.61 (EEDATA), U11.3 (DI)
unnamed: C36.1, U10.2 (OSCI), X2.3 (OSC2)
unnamed: C37.1, U10.3 (OSCO), X2.1 (OSC1)
unnamed: R31.1, U10.6 (REF)
unnamed: C29.1, C30.1, L3.1, U10.4 (VPHY)
unnamed: C31.1, C32.1, L4.1, U10.9 (VPLL)
unnamed: C34.2, R30.2, U10.14 (~RESET)
unnamed: R32.1, R33.2, U11.1 (DO)
unnamed: C45.2, R40.2, ST_RESET1.2, U12.25 (NRST)
unnamed: C46.2, R41.1, U12.23 (PH0), X3.3 (OSC2)
unnamed: C47.2, R41.2, U12.24 (PH1), X3.1 (OSC1)
unnamed: C71.2, U12.71 (VCAP_1)
unnamed: C72.2, U12.106 (VCAP_2)
unnamed: R52.2, U13.1 (RSETE)
unnamed: C75.1, U13.36 (RSTI)
unnamed: C73.2, U13.10 (XI), X4.3 (OSC2)
unnamed: C74.2, U13.11 (XO), X4.1 (OSC1)
unnamed: R59.2, U14.1 (RSETE)
unnamed: C78.1, U14.36 (RSTI)
unnamed: C76.2, U14.10 (XI), X5.3 (OSC2)
unnamed: C77.2, U14.11 (XO), X5.1 (OSC1)
unnamed: R65.2, R68.1, U15.1 (A0)
unnamed: R66.2, R69.1, U15.2 (A1)
unnamed: R67.2, R70.1, U15.3 (A2)
unnamed: R75.2, U16.9 (AD0)
unnamed: C83.2, U16.20 (CPOUT)
unnamed: C84.1, U16.10 (REGOUT)
VSS: 1V8_PWR1.1 (K), 3V3_PWR1.1 (K), 5V_PWR1.1 (K), AKINA_JTAG1.4, AKINA_JTAG1.8, AKINA_JTAG1.10, AKINA_RESET1.1, BAT1.2 (-), BOOT_MODE1.3, BOOT_MODE1.4, BOOT_MODE2.3, BOOT_MODE2.4, BTB100x1.14, BTB100x1.26, BTB100x1.50, BTB100x1.69, BTB100x1.76, BTB100x1.100, BTB100x1.109, BTB100x1.110, BTB100x1.111, BTB100x1.150, BTB100x1.164, BTB100x1.200, C1.2, C2.2, C3.2, C4.2, C5.2, C6.2, C7.2, C8.2, C9.1, C10.1, C11.1, C12.1, C13.1, C14.2, C15.2, C16.2, C17.2, C22.2, C23.2, C24.1, C25.1, C26.1, C27.1, C28.2, C29.2, C30.2, C31.2, C32.2, C33.1, C34.1, C35.2, C36.2, C37.2, C38.1, C39.1, C40.1, C41.1, C42.1, C43.1, C44.1, C45.1, C46.1, C47.1, C48.2, C49.2, C50.2, C51.2, C52.2, C53.2, C54.2, C55.2, C56.2, C57.2, C58.2, C59.2, C60.2, C61.2, C62.2, C63.2, C64.2, C65.2, C67.2, C68.2, C69.2, C70.2, C71.1, C72.1, C73.1, C74.1, C75.2, C76.1, C77.1, C78.2, C79.2, C80.2, C81.2, C82.2, C83.1, C84.2, C85.2, C86.2, C87.2, C96.1, C97.1, C98.1, C99.1, C100.2, C101.2, ESD1.2 (A2), ESD2.2 (A2), ESD3.2 (A2), ESD4.2 (A2), ETH1.8 (P8/GND), ETH1.13 (SH), ETH1.14 (SH), ETH2.8 (P8/GND), ETH2.13 (SH), ETH2.14 (SH), J3.20, J4.2, J4.18, J4.20, J5.10, J5.19, J5.20, J7.17, J7.19, J8.13, J11.3, J11.4, J11.7, J11.8, J11.11, J11.12, J14.2, J14.4, J15.2, J15.4, J16.2, J16.4, J17.2, J17.4, J18.2, J18.4, J20.2, J20.4, J20.6, J21.2, J21.4, J22.2, J22.4, J22.6, J23.2, J23.4, J23.6, J24.2, J25.2, J26.2, J27.2, J28.3, LED1.1 (K), LED2.1 (K), LED3.1 (K), LED4.1 (K), LED5.1 (K), LED6.1 (K), LED7.1 (K), LED8.1 (K), LED9.1 (K), LED10.1 (K), LED11.1 (K), LED12.1 (K), Q1.2 (E), R5.1, R7.1, R9.1, R10.1, R11.1, R13.1, R14.1, R19.1, R22.1, R24.1, R31.2, R52.1, R59.1, R68.2, R69.2, R70.2, R75.1, R99.1, R139.1, SCREEN1.1 (GND), SD1.6 (VSS), SD1.10 (GND), SD1.11 (GND), SD1.12 (GND), SD1.13 (GND), ST_JTAG1.4, ST_JTAG1.8, ST_JTAG1.10, ST_RESET1.1, T1.1, T2.1, T3.1, T4.1, TP2.1, TP5.1, TP8.1, TP11.1, TP13.1, TP17.1, TP19.1, TP21.1, TP26.1, TP28.1, TP30.1, U1.2 (GND), U2.2 (GND), U3.2 (GND), U4.1 (NC), U4.4 (GND), U5.1 (NC), U5.4 (GND), U6.16 (GND), U7.3 (GND), U8.3 (GND), U9.3 (GND), U10.1 (GND), U10.5 (GND), U10.10 (AGND), U10.11 (GND), U10.13 (TEST), U10.15 (GND), U10.25 (GND), U10.35 (GND), U10.47 (GND), U10.51 (GND), U11.2 (VSS), U12.16 (VSS), U12.31 (VSSA), U12.38 (VSS), U12.51 (VSS), U12.61 (VSS), U12.83 (VSS), U12.94 (VSS), U12.107 (VSS), U12.120 (VSS), U12.130 (VSS), U13.3 (GND), U13.9 (GND), U13.13 (GND), U13.18 (GND), U13.20 (GND), U13.37 (GND), U13.41 (GND), U13.44 (GND), U13.48 (GND), U14.3 (GND), U14.9 (GND), U14.13 (GND), U14.18 (GND), U14.20 (GND), U14.37 (GND), U14.41 (GND), U14.44 (GND), U14.48 (GND), U15.4 (VSS), U15.7 (WP), U16.1 (CLKIN), U16.11 (FSYNC), U16.18 (GND), U16.25 (GND), U17.4 (GND), USB1.1 (A1/B12), USB1.12 (A12/B1), USB1.S1 (SHELL), USB1.S2 (SHELL), USB1.S3 (SHELL), USB1.S4 (SHELL), USB2.1 (A1/B12), USB2.12 (A12/B1), USB2.S1 (SHELL), USB2.S2 (SHELL), USB2.S3 (SHELL), USB2.S4 (SHELL), X1.2 (GND), X2.2 (GND), X2.4 (GND), X3.2 (GND), X3.4 (GND), X4.2 (GND), X4.4 (GND), X5.2 (GND), X5.4 (GND)

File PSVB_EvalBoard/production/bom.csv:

Designator,Footprint,Quantity,Value,LCSC Part #
,zhengu_logo,1,,
1V8_PWR,0603,1,0603 1V8_PWR,
3V3_PWR,0603,1,0603 3V3_LED,
5V_PWR1,0603,1,0603 5V_LED,
"AKINA_JTAG1, ST_JTAG1",PinHeader_2x05_P2.54mm_Vertical,2,~,
"AKINA_RESET1, ST_RESET1",SW_SPST_CK_RS282G05A3,2,KEY,
BAT1,CR1220_Holder,1,CR1220-2,
BEEP1,BEEP_4317,1,BUZZER,
"BOOT_MODE1, BOOT_MODE2",SW_DIP_SPSTx02_Slide_6.7x6.64mm_W8.61mm_P2.54mm_LowProfile,2,SW_SMD_2P-2.54mm,
BTB100x1,BTB100PINx2_FemaleConnector,1,BTB100PINx2_IC_Adapter,
C1,CP_Elec_6.3x7.7,1,47uF,
"C10, C17",0603,2,0603 4.7uF/1%,
"C100, C38, C39, C40, C41, C42, C43, C44, C49, C50, C51, C52, C53, C54, C55, C56, C57, C58, C80, C81, C84, C85, C86, C87, C88, C89, C90, C91, C92, C93, C94, C95, C96, C97, C98, C99",0603,36,0.1uF,
C101,0603,1,10uF,
"C11, C12, C14, C18, C19, C20, C21, C23, C29, C31, C34, C35, C45, C48, C71, C72, C75, C78, C79",0603,19,0603 0.1uF/16V,
"C13, C22, C24, C30, C32, C59",0603,6,0603 4.7uF/16V,
C15,0603,1,0603 0.01uF/16V,
C16,0603,1,0603 30P/16V,
C2,CP_Elec_6.3x7.7,1,22uF,
"C25, C26, C27, C28",0603,4,0603 10uF/16V,
"C3, C4, C5, C6, C7, C8",0603,6,0603 1uF/16V,
C33,0603,1,0603 3.3uF/16V,
"C36, C37",0603,2,0603 27pF/16V,
"C46, C47",0603,2,0603 10pF/16V,
"C60, C61, C62, C63, C64, C65, C67, C68, C69, C70",0603,10,4.7uF,
"C73, C74, C76, C77",0603,4,0603 20PF/16V,
C82,0603,1,0.01uF,
C83,0603,1,2.2nF,
C9,0603,1,0603 0.1uF/1%,
D1,D_SOD-123,1,1N4148,
"ESD1, ESD2, ESD3, ESD4",D_SOD-323_HandSoldering,4,SD24C-TP,
"ETH1, ETH2",RJ45_HanRun_HR911105A,2,HR911105A,
F1,1206,1,1206 10V/2A,
"J1, J19",PinHeader_2x04_P2.54mm_Vertical,2,~,
"J10, J12, J3, J4, J5, J6, J7, J8, J9",PinHeader_2x10_P2.54mm_Vertical,9,PIN20,
J11,PinHeader_2x06_P2.54mm_Vertical,1,PIN12_2x6,
"J13, J29, J30, J31",PinHeader_2x03_P2.54mm_Vertical,4,PIN6_2x3,
"J14, J15, J16, J17, J18",PinHeader_1x04_P2.54mm_Vertical,5,~,
J2,PinHeader_1x02_P2.54mm_Vertical,1,PIN2,
"J20, J21, J22, J23",PinHeader_1x06_P2.54mm_Vertical,4,~,
"J24, J25, J26, J27, J28",PinHeader_1x03_P2.54mm_Vertical,5,~,
"KEY1, KEY2, KEY3, KEY4, KEY6, KEY7, KEY8, KEY9",SW_SPST_CK_RS282G05A3,8,SW_Push,
KEY5,5Axises_Key,1,5Axises_KEY,
L1,SWPA3010,1,2.2uH/1A,
"L2, L3, L4",0603,3,6.8nH/500mA,
"LED1, LED2",0603,2,YELLOW,
"LED10, LED11, LED12, LED3, LED4, LED5, LED6, LED7, LED8, LED9",0603,10,LD271,
"MARK1, MARK2, MARK3, MARK4",Fiducial_1mm_Mask2mm,4,Fiducial_1mm_Mask2mm,
POWER1,SelfLock_Switch,1,SW_SELF_LOCK_5.8mm-5.8mm-10mm,
Q1,SOT-23,1,S9013,
R1,0603,1,0603 5K/1%,
"R10, R11, R12, R13, R14, R15, R17, R18, R19, R20, R21, R22, R23, R24, R25, R26, R27, R28, R29",0603,19,0603 0R/1%,
"R100, R101, R102, R103, R104, R105, R106, R107, R108, R109, R110, R111, R112, R113, R114, R115, R116, R117, R118, R119, R120, R121, R122, R132, R133, R93, R94, R95",0603,28,0R/1%,
"R123, R124, R125, R126, R127, R128, R129, R130, R65, R66, R67, R68, R69, R70, R71, R72, R73, R74, R77, R78, R79, R80, R81, R90, R91, R92, R96, R97, R99",0603,29,10K/1%,
R131,0603,1,0603 100R/1%,
"R134, R135, R136, R137, R138, R2, R3",0603,7,0603 1K/1%,
"R139, R140, R141, R142, R143, R144, R145, R146, R147, R148, R149, R150, R151, R152, R153, R154, R155, R156, R157, R16, R160, R161, R162, R164, R165, R166, R167, R168, R169, R170, R171, R172, R173, R174, R175, R176, R177, R178, R179, R180, R181, R183, R184, R185, R186, R187, R188, R189, R190, R191, R192, R193, R194, R195, R196, R197, R203, R204, R207, R208, R213, R214, R215, R216, R217, R218, R219, R220, R221, R222, R223, R224, R225, R226, R227, R30, R33, R34, R35, R36, R37, R38, R39, R40, R42, R43, R44, R45, R60, R61, R62, R63, R64, R76",0603,94,0603 10K/1%,
"R158, R159, R163, R182, R198, R199",0603,6,0603 47K/1%,
R31,0603,1,0603 12K/1%,
R32,0603,1,0603 2K/1%,
"R4, R8",0603,2,0603 500K/1%,
R41,0603,1,0603 1M/1%,
"R46, R47, R53, R54",0603,4,510R/1%,
"R48, R49, R50, R51, R55, R56, R57, R58",0603,8,49R9/1%,
"R5, R7",0603,2,0603 160K/1%,
"R52, R59",0603,2,18K/1%,
R6,0603,1,0603 200K/1%,
R75,0603,1,4.7K/1%,
"R82, R83, R84, R85, R86, R87, R88, R89",0603,8,1K/1%,
R9,0603,1,0603 160K/16V,
R98,GT36516,1,A1050,
"RS1, RS2",1206,2,0603 10mR/1%,
SCREEN1,PinHeader_1x08_P2.54mm_Vertical,1,2.4In_TFT_Screen,
SD1,TF-SMD_TF-02,1,~,
SW1,SW_DIP_SPSTx04_Slide_6.7x11.72mm_W8.61mm_P2.54mm_LowProfile,1,~,
"T1, T2, T3, T4",M3_Whole,4,~,
"TP1, TP10, TP11, TP12, TP13, TP14, TP15, TP16, TP17, TP18, TP19, TP2, TP20, TP21, TP22, TP23, TP24, TP25, TP26, TP27, TP28, TP29, TP3, TP30, TP4, TP5, TP6, TP7, TP8, TP9",TestPoint_Pad_D1.5mm,30,TestPoint_1.5mm,
"U1, U2, U3",SOT-23-5_HandSoldering,3,SGM2036-ADJ,
U10,LQFP-64_10x10mm_P0.5mm,1,~,
U11,SOT-23-6_Handsoldering,1,93LC56BT-IOT,
U12,LQFP-144_20x20mm_P0.5mm,1,STM32F429ZETx,
"U13, U14",LQFP-64_10x10mm_P0.5mm,2,CH395Q,
U15,SOIC-8_3.9x4.9mm_P1.27mm,1,24LC64ISN,
U16,QFN-24-1EP_4x4mm_P0.5mm_EP2.7x2.6mm,1,MPU6050,
U17,SOIC-8_5.275x5.275mm_P1.27mm,1,W25Q128JVSIQ,
"U4, U5",TSSOP-8_4.4x3mm_P0.65mm,2,INA240A1PWR,
U6,SOIC-16_3.9x9.9mm_P1.27mm,1,TM7707,
U7,SOT-23,1,REF3030,
U8,SOT-23,1,REF3025,
U9,SOT-23,1,REF3012,
"USB1, USB2",USB_C_PIN16,2,USB_C_16PIN-Connector,
X1,Oscillator_SMD_EuroQuartz_XO91-4Pin_7.0x5.0mm_HandSoldering,1,2.4576Mhz,
X2,Oscillator_SMD_EuroQuartz_XO32-4Pin_3.2x2.5mm_HandSoldering,1,12Mhz_Passive_3225,
X3,Oscillator_SMD_EuroQuartz_XO32-4Pin_3.2x2.5mm_HandSoldering,1,16Mhz_Passive_3225,
"X4, X5",Oscillator_SMD_EuroQuartz_XO32-4Pin_3.2x2.5mm_HandSoldering,2,30Mhz_3225,

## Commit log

2023-04-18 Updated new PSVB hardware design.
2023-04-21 update PSVB hardware design
2023-04-21 Almost finished the schematic design
2023-04-23 update PCB design
2023-04-28 Updated PCB design
2023-05-04 updated PCB design-2023-5-24
2023-05-05 almost finished the PCB design
2023-05-06 80 lines unconnected
2023-05-06 almost finished
2023-05-08 i need one day more
2023-05-09 Generated some PCB outputs.
2023-05-09 24 lines not connected, almost done.
2023-05-10 Finished the PCB layout
2023-05-11 Did some modification.
2023-05-12 Fixed some issues.
2023-05-12 Finished PCB layout.
2023-05-12 Project finished.
2023-05-15 Finished the modification, still need some more silks.k
2023-05-16 Fix some errors.
2023-05-16 Updated silkscreen.
2023-05-17 Finished the bottom silkscreen.
2023-05-17 Did some modification on top-silkscreen.
2023-05-17 Finished PCB design.
2023-05-17 Gerber generated.
2023-05-17 Finished all the things.
2023-05-18 Finished.
